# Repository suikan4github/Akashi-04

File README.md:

# Akashi-04
Audio board for Nucleo-G431RB

## Functionality
This board is designed to provide the audio functionality for the  STM32 series MCU. 
The connectors can be directly mounted on the Nucleo 64 series board and employs I2S interface of STM32 MCU.
This board supports following Nucleo :
- STM32F446RE
- STM32G431RB

The design can be retrieved from the [github](https://github.com/suikan4github/Akashi-04) repository.

These functionalities are tested with following codec board as with I2C control line. 
- [UMB-ADAU1361A](http://dsps.shop-pro.jp/?pid=82798273)

## Development
- [KiCad 5.1](http://kicad.org/blog/2019/03/KiCad-5.1.0-Release/)
- [Nucleo G431RB](https://www.st.com/en/evaluation-tools/nucleo-g431rb.html)
- [Nucleo F446RE](https://www.st.com/en/evaluation-tools/nucleo-f446re.html)

The schematics [can be downloaded](docs/Akashi-04.pdf) as PDF format. 

The configuration of special ports are :
- I2S2 : Slave TX
- I2S3 : Slave RX
- PB7 : EXTI to detect the I2S WS edge. 
- PC9 : Open Drain output. To save the struggled I2C device.

## I2C address
By default, the I2C device address are configured as ***0x38*** ( 7bit address ). 
If you want to change, you should modify the short bridge as following : 

| JP1    | JP2    | Address |
---------|--------|---------|
| Closed | Closed | 0x38    |
| Open   | Closed | 0x39    |
| Closed | Open   | 0x3A    |
| Open   | Open   | 0x3B    |

Note that R3 and R4 are needed if JP1 and JP2 are cut, respectively

## Usage
To clone this project, follow :
```
git clone repository-of-this-project
git submodule update
```

The sample programs are published as [murasaki_samples_audio](https://github.com/suikan4github/murasaki_samples_audio) repositories. 

 To use these repository, follow the sequence :
 1. Clone the murasaki_samples_audio repository
 1. Import to CubeIDE

Caution : Because of the height of the capacitor, the stacked Arduino board may contact to the capacitor. 

## License
This PCB design is released under the [Creative Commons Attribution 4.0 International license](https://creativecommons.org/licenses/by/4.0/). 
You are welcome to use this design for commercial purposes.

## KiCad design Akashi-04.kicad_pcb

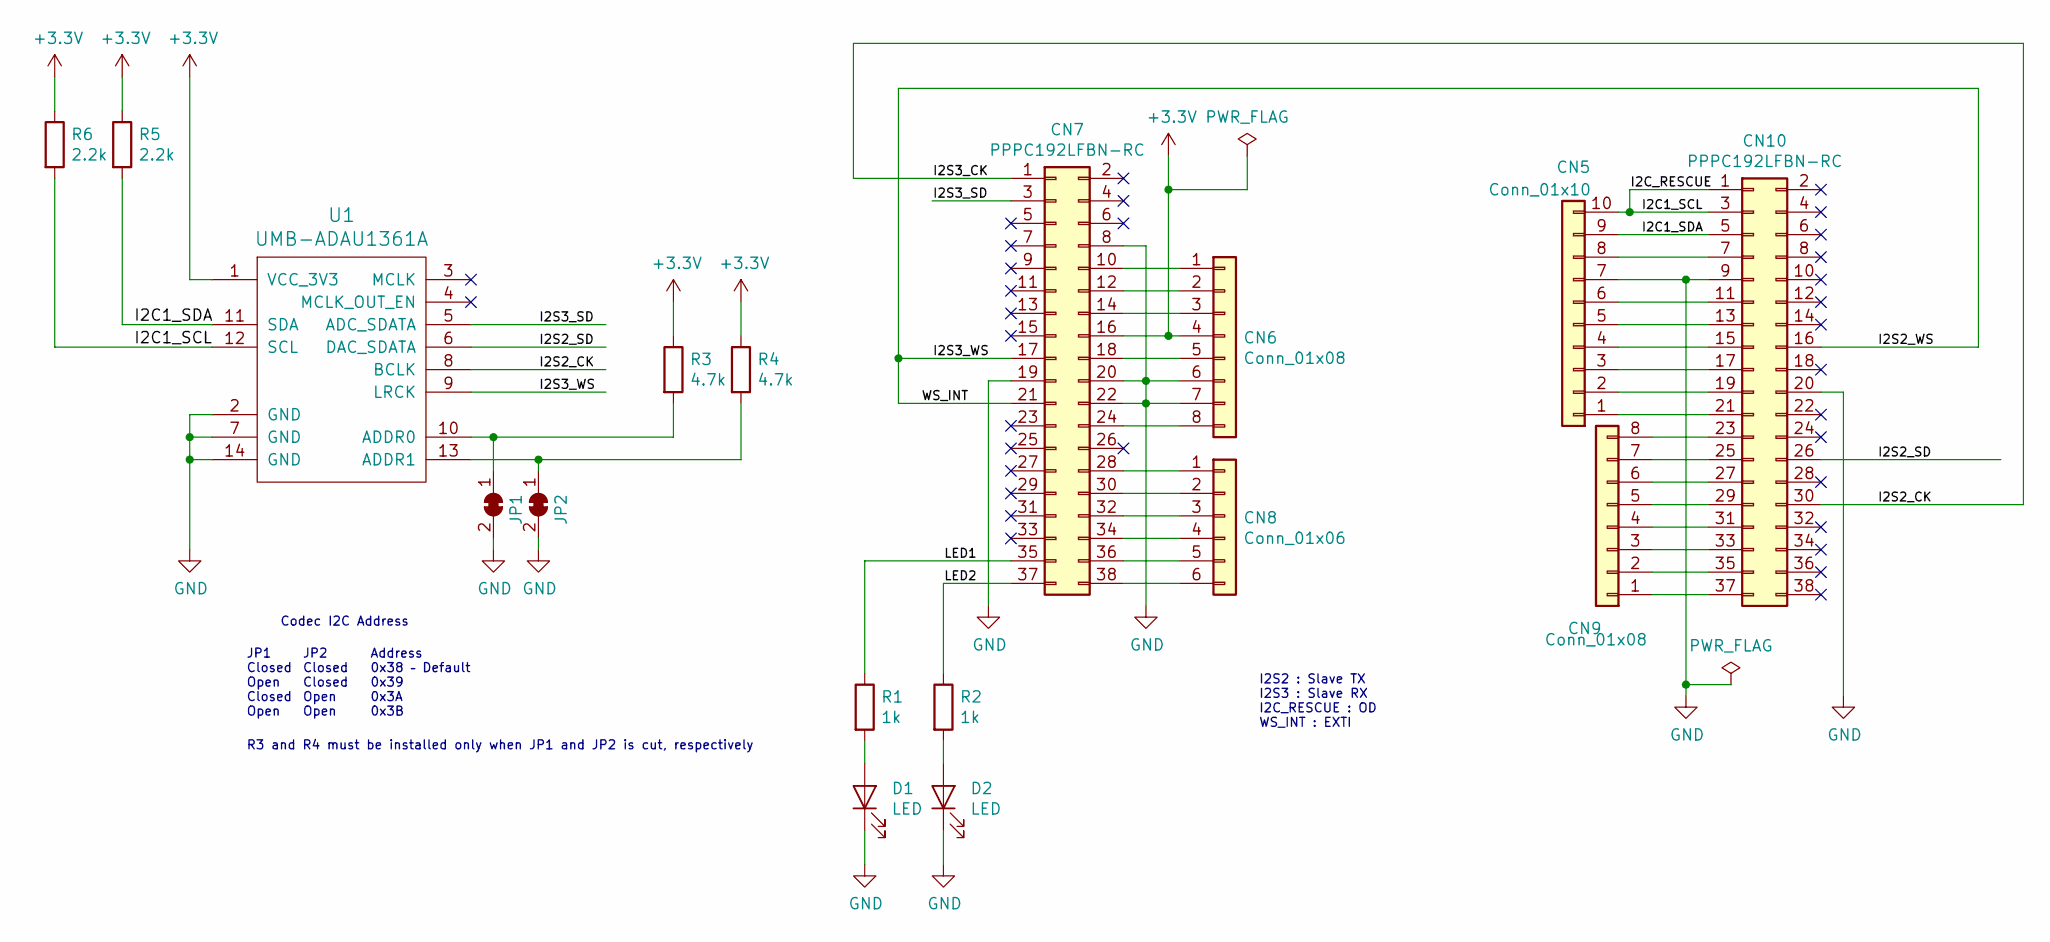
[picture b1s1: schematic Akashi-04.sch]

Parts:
CN5: Conn_01x10; PinHeader_1x10_P2.54mm_Vertical
CN6, CN9: Conn_01x08; PinHeader_1x08_P2.54mm_Vertical
CN7, CN10: PPPC192LFBN-RC; PinSocket_2x19_P2.54mm_Vertical
CN8: Conn_01x06; PinHeader_1x06_P2.54mm_Vertical
D1, D2: LED; LED_D3.0mm_Clear
JP1, JP2: SolderJumper_2_Bridged; SolderJumper-2_P1.3mm_Bridged_RoundedPad1.0x1.5mm
R1, R2: 1k; R_Axial_DIN0207_L6.3mm_D2.5mm_P10.16mm_Horizontal
R3, R4: 4.7k; R_Axial_DIN0207_L6.3mm_D2.5mm_P10.16mm_Horizontal
R5, R6: 2.2k; R_Axial_DIN0207_L6.3mm_D2.5mm_P10.16mm_Horizontal
U1: UMB-ADAU1361A

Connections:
+3V3: CN6.4, CN7.16, R3.1, R4.1, R5.1, R6.1, U1.1 (VCC_3V3)
/I2C1_SCL: CN5.10, CN10.1, CN10.3, R6.2, U1.12 (SCL)
/I2C1_SDA: CN5.9, CN10.5, R5.2, U1.11 (SDA)
/I2S2_CK: CN7.1, CN10.30, U1.8 (BCLK)
/I2S2_SD: CN10.26, U1.6 (DAC_SDATA)
/I2S2_WS: CN7.17, CN7.21, CN10.16, U1.9 (LRCK)
/I2S3_SD: CN7.3, U1.5 (ADC_SDATA)
/LED1: CN7.35, R1.1
/LED2: CN7.37, R2.1
GND: CN5.7, CN6.6, CN6.7, CN7.8, CN7.19, CN7.20, CN7.22, CN10.9, CN10.20, D1.1 (K), D2.1 (K), JP1.2 (B), JP2.2 (B), U1.2 (GND), U1.7 (GND), U1.14 (GND)
unnamed: CN6.1, CN7.10
unnamed: CN6.2, CN7.12
unnamed: CN6.3, CN7.14
unnamed: CN6.5, CN7.18
unnamed: CN6.8, CN7.24
unnamed: CN7.28, CN8.1
unnamed: CN7.30, CN8.2
unnamed: CN7.32, CN8.3
unnamed: CN7.34, CN8.4
unnamed: CN7.36, CN8.5
unnamed: CN7.38, CN8.6
unnamed: CN5.8, CN10.7
unnamed: CN5.6, CN10.11
unnamed: CN5.5, CN10.13
unnamed: CN5.4, CN10.15
unnamed: CN5.3, CN10.17
unnamed: CN5.2, CN10.19
unnamed: CN5.1, CN10.21
unnamed: CN9.8, CN10.23
unnamed: CN9.7, CN10.25
unnamed: CN9.6, CN10.27
unnamed: CN9.5, CN10.29
unnamed: CN9.4, CN10.31
unnamed: CN9.3, CN10.33
unnamed: CN9.2, CN10.35
unnamed: CN9.1, CN10.37
unnamed: D1.2 (A), R1.2
unnamed: D2.2 (A), R2.2
unnamed: JP1.1 (A), R3.2, U1.10 (ADDR0)
unnamed: JP2.1 (A), R4.2, U1.13 (ADDR1)

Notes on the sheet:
JP1 Closed Open Closed Open
JP2 Closed Closed Open Open
Address 0x38 – Default 0x39 0x3A 0x3B
Codec I2C Address
I2S2 : Slave TX I2S3 : Slave RX I2C_RESCUE : OD WS_INT : EXTI
R3 and R4 must be installed only when JP1 and JP2 is cut, respectively

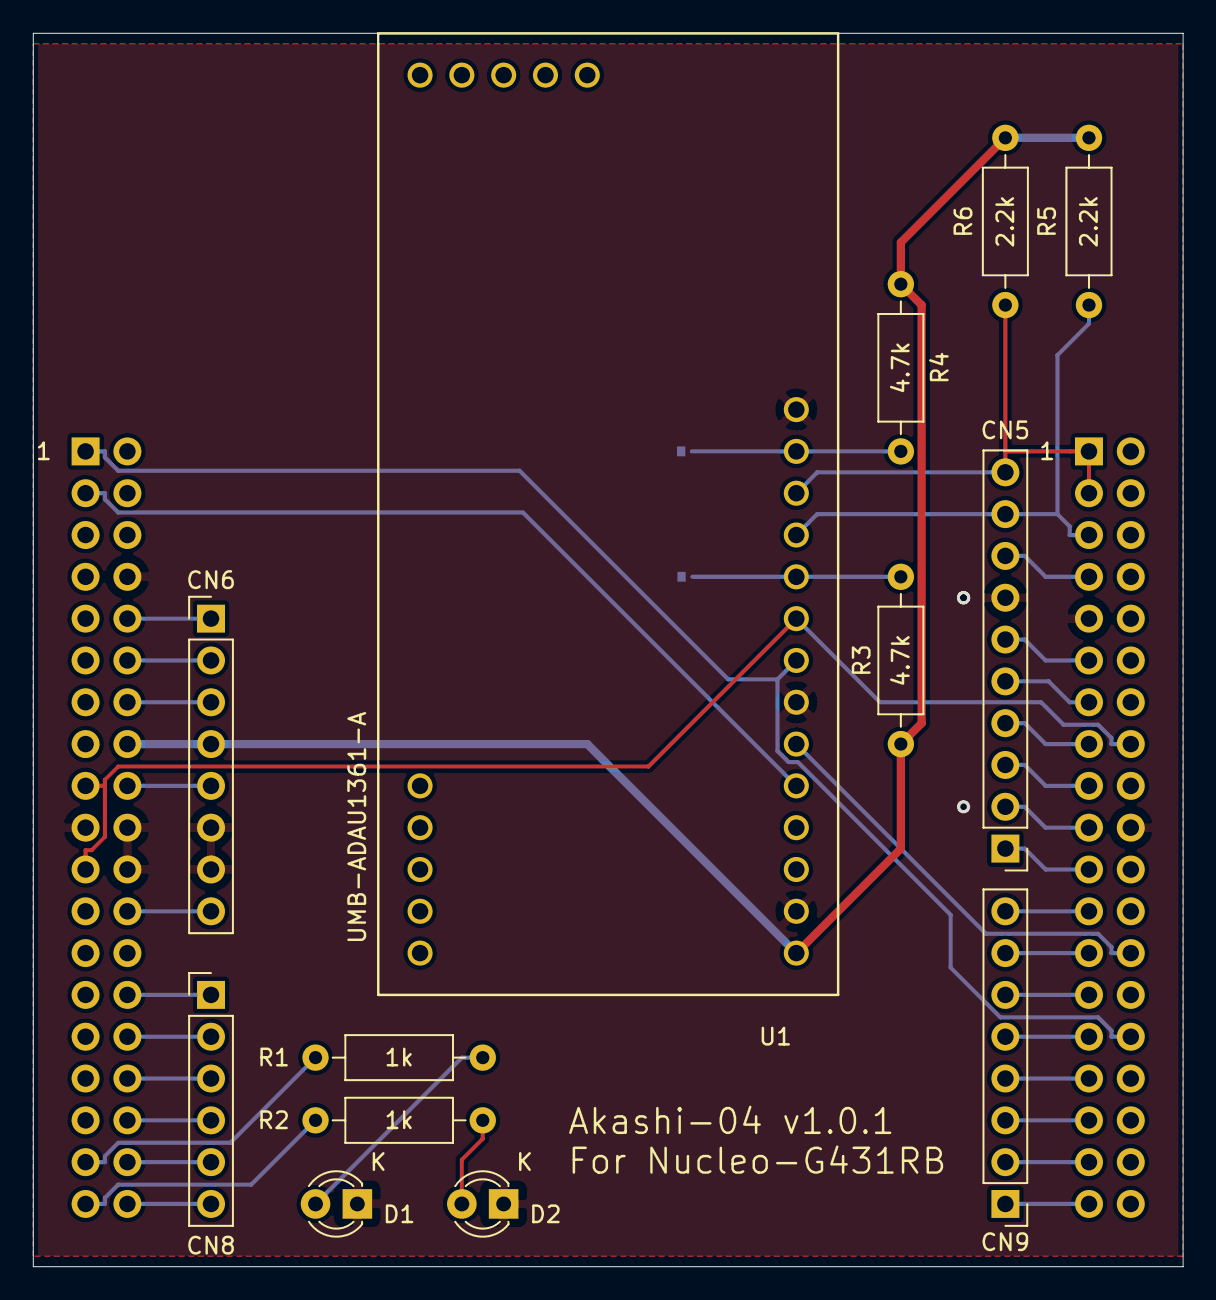
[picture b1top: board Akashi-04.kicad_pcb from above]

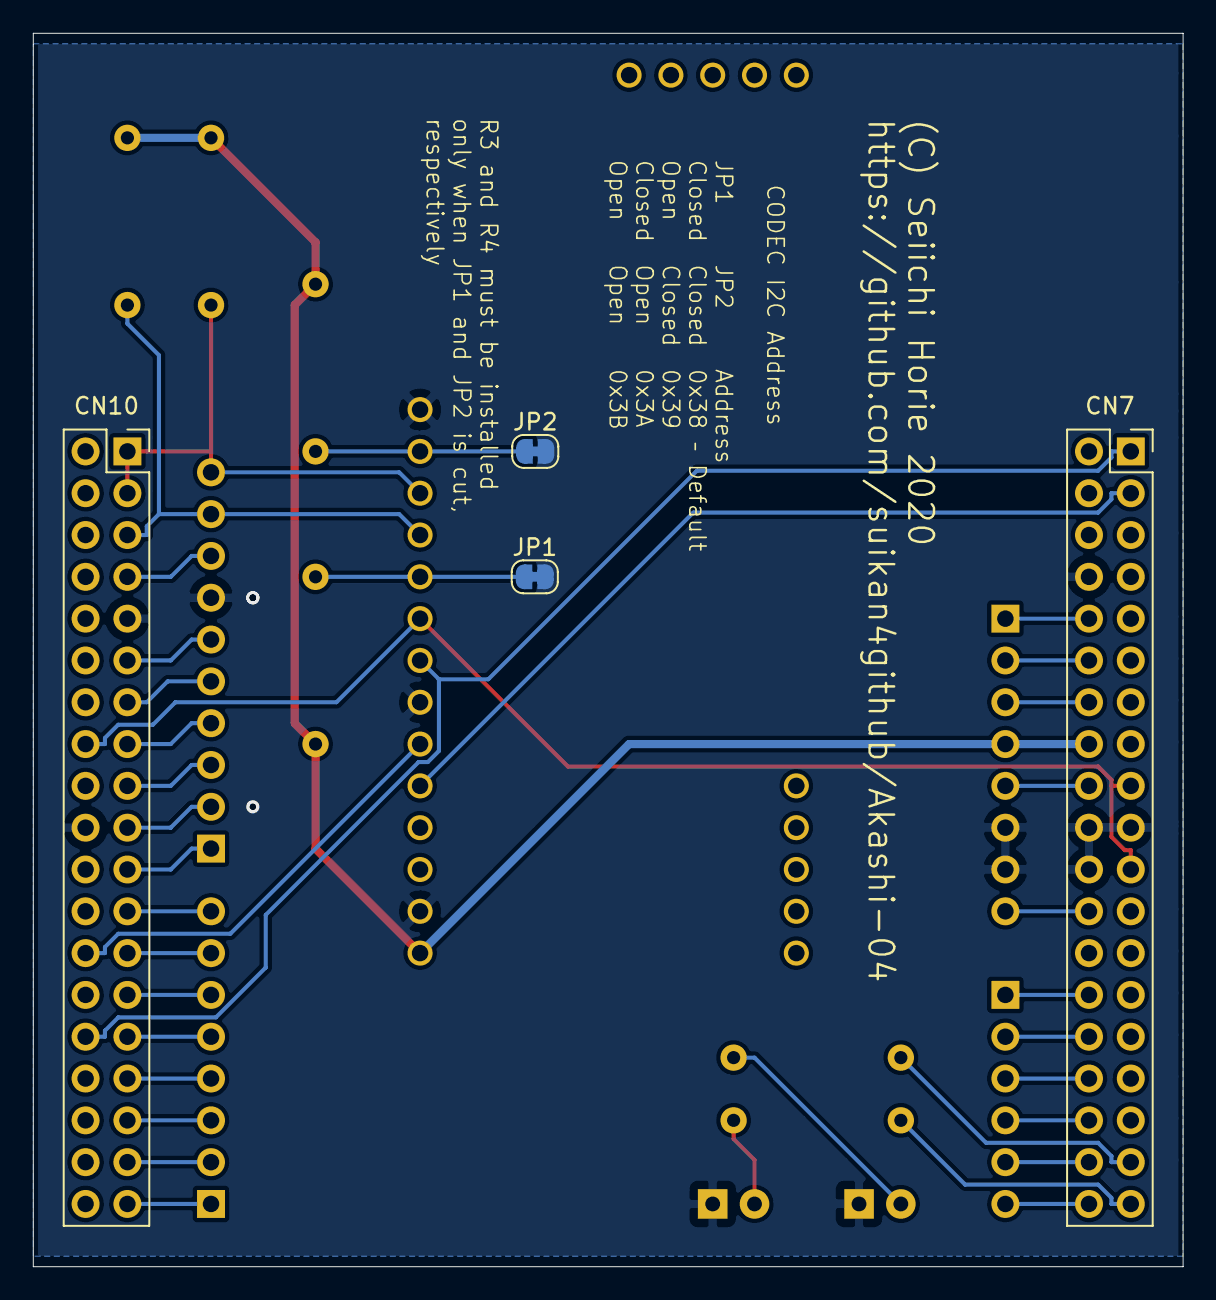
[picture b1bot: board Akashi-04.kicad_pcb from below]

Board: 2 copper layers, 69.9 x 74.9 mm, 17 parts (4 on the bottom side), 40 nets.

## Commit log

2020-02-16 Revert "Initial commit"
    This reverts commit f868d28a5865c707f290b649e922866782d35e7e.
2020-02-16 Rough design
2020-02-16 Designe done
2020-02-23 Added I2C clock rescue
2020-03-01 Added rescue line of I2C and I2S WS int
    I2C rescue is needed to toggle the I2C SCL inc case of
    the device is stretching signal by fault.
    I2S WS int is needed to start the audio in the correct timing.
2020-03-01 Generated v1.0.0 gerber
2020-03-02 Removed gabage.
2020-03-02 Fixed problem.
2020-03-12 Moved resister
2020-03-12 Moved label
2020-03-20 Added board photo.
2020-03-20 Update changelog
2021-11-10 Update README.md
    https://forum.kicad.info/t/warning-avoid-all-links-to-kicad-pcb-org-use-kicad-org/31521
